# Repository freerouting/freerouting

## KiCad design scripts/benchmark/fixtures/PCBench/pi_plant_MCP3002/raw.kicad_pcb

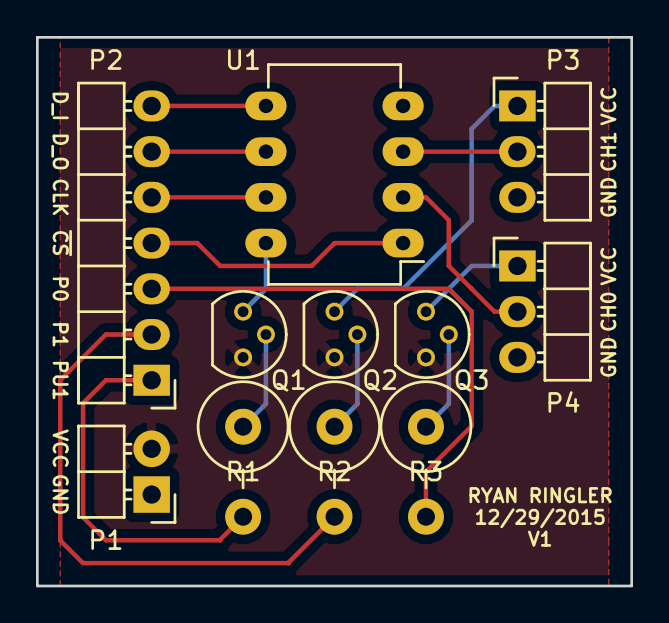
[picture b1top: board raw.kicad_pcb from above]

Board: 2 copper layers, 33.0 x 30.5 mm, 11 parts (0 on the bottom side), 17 nets.

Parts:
P1: CONN_01X02; Pin_Header_Angled_1x02_No_Pins
P2: CONN_01X07; Pin_Header_Angled_1x07_No_Pins
P3, P4: CONN_01X03; Pin_Header_Angled_1x03_No_Pins
Q1, Q2, Q3: 2N3904; TO-92_Molded_Narrow
R1, R2, R3: 1K; Resistor_Vertical_RM5mm
U1: MCP3002; DIP-8_W7.62mm_LongPads

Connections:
GND: P1.1, P3.3, P4.3, U1.4
unnamed: P2.1, R1.2
unnamed: P2.2, R2.2
unnamed: P2.3, R3.2
unnamed: P2.4, U1.1
unnamed: P2.5, U1.7
unnamed: P2.6, U1.6
unnamed: P2.7, U1.5
unnamed: P3.1, Q2.1
unnamed: P3.2, U1.3
unnamed: P4.1, Q3.1
unnamed: P4.2, U1.2
unnamed: Q1.1, U1.8
unnamed: Q1.2, R1.1
unnamed: Q2.2, R2.1
unnamed: Q3.2, R3.1
VCC: P1.2, Q1.3, Q2.3, Q3.3

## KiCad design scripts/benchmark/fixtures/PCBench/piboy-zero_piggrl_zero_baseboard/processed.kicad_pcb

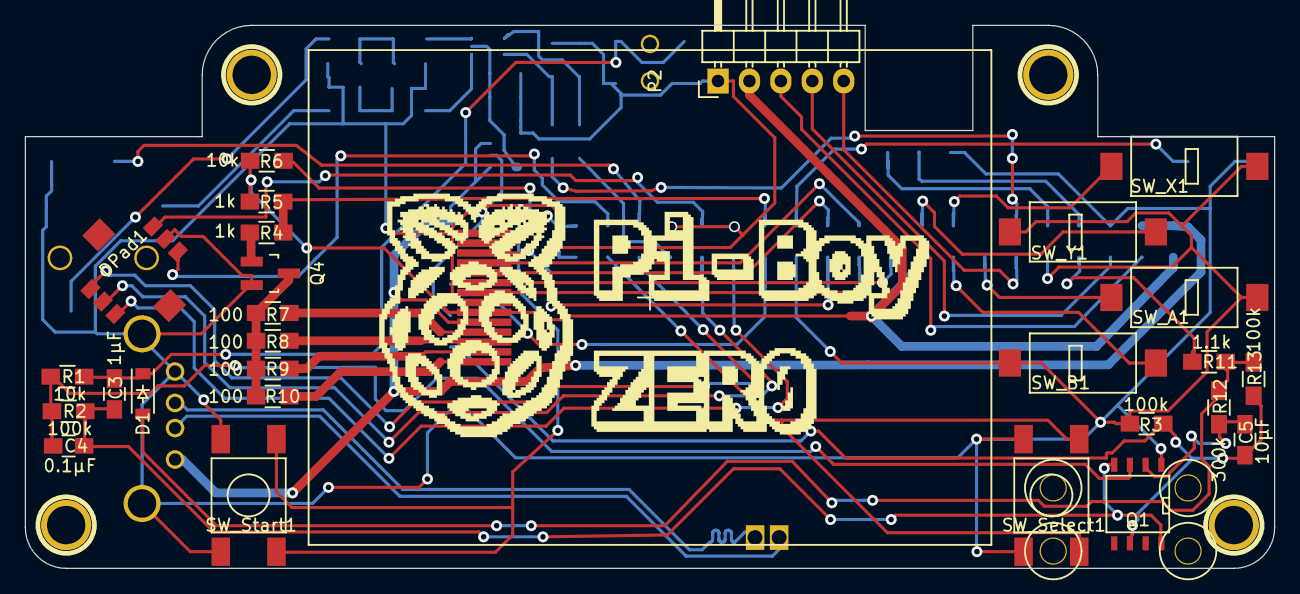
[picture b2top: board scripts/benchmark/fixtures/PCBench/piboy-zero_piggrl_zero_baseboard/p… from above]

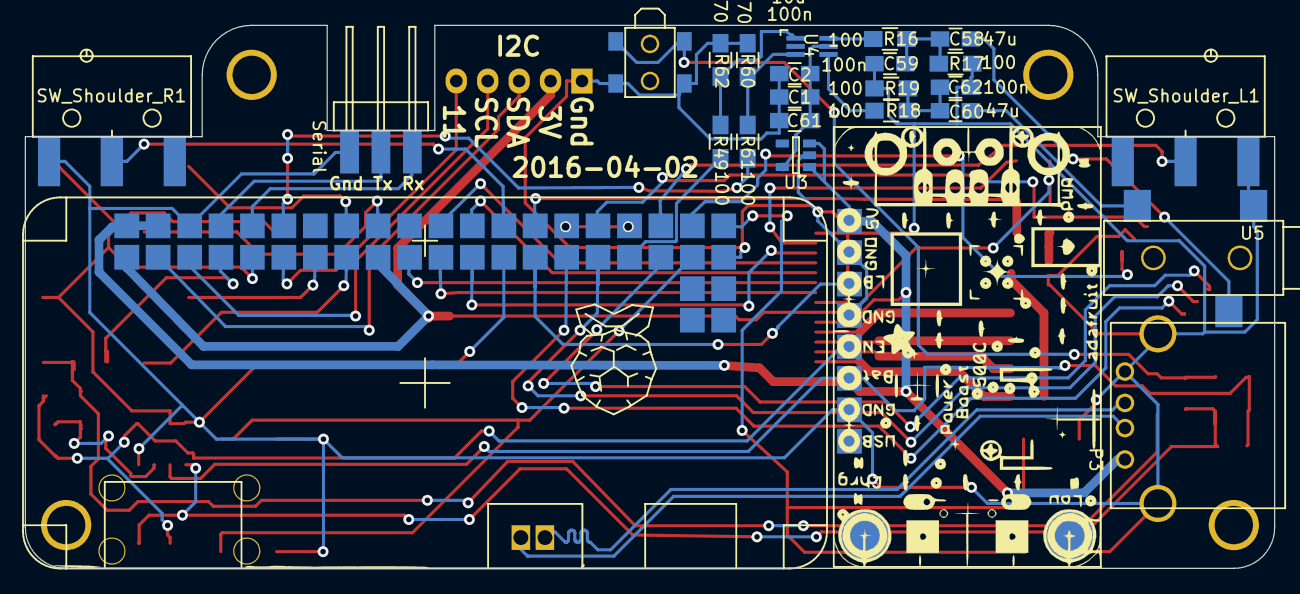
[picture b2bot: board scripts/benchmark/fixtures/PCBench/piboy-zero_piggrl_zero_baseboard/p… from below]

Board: 2 copper layers, 101.0 x 43.9 mm, 57 parts (25 on the bottom side), 55 nets.

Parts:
1PIN, 1PIN_2, 1PIN_3, 1PIN_4: P***; 1pin
C1: 10u; C_0805_HandSoldering
C2: 10n; C_0805_HandSoldering
C3: 1µF; C_0805_HandSoldering
C4: 0.1µF; C_0805_HandSoldering
C5: 10µF; C_0805_HandSoldering
C58, C60: 47u; C_0805_HandSoldering
C59, C61, C62: 100n; C_0805_HandSoldering
D1: D; SOD-123
DPad1: SKRHAAE010
P1: PowerBoost 500c; Powerboost500c
P2: I2C; Pin_Header_Angled_1x05
P3: USB_A
P4: Serial; 1x3_smd_pinheader
Q1: IRF7309IPBF; SOIC-8-N
Q4: MMBT2222; SOT-23_Handsoldering
R1, R6: 10k; R_0805_HandSoldering
R2, R3, R13: 100k; R_0805_HandSoldering
R4, R5: 1k; R_0805_HandSoldering
R7, R8, R9, R10, R16, R17, R18, R19, R49, R61: 100; R_0805_HandSoldering
R11: 1.1k; R_0805_HandSoldering
R12: 300k; R_0805_HandSoldering
R60, R62: 470; R_0805_HandSoldering
SW1: SW_PUSH; btn_1571262-1
SW_A1: SW_PUSH; Omron_D2LS_21_woKeyHoles
SW_B1: SW_PUSH; Omron_D2LS_21_woKeyHoles
SW_Select1: SW_PUSH; smd_push_button
SW_Shoulder_L1: SW_PUSH; Omron_D2FS_FTN_mirror
SW_Shoulder_R1: SW_PUSH; Omron_D2FS_FTN
SW_Start1: SW_PUSH; smd_push_button
SW_X1: SW_PUSH; Omron_D2LS_21_woKeyHoles
SW_Y1: SW_PUSH; Omron_D2LS_21_woKeyHoles
U1: gpio-header_zero; raspberry-zero
U2: 2.2_tft_ili9340; TM022HDH26
U3: Regulator_LP2980; SOT-23-5
U4: NC7WZ16_Dual_Buffer; SC-70-6_Handsoldering
U5: audio_jack; audio_smd_SJ-3523-SMT-TR

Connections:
+2V5: C1.1, C2.1, C61.2, U3.5, U4.5
+3V3: P2.2, R4.2, R6.2, U1.1, U1.17, U2.9
+5V: P1.8, P3.1, U1.2, U1.4, U2.10, U3.1, U3.3
+BATT: C4.2, P1.3, Q1.3, R1.2, R2.2
/LowBatOut: P1.6, U1.27
/PWM_backlight: R4.1, R5.2, U1.28
/Rasberppy B+ audio/Aud_PWM0: R61.2, U1.12
/Rasberppy B+ audio/Aud_PWM1: R49.2, U1.33
/USB_D+: P3.3, U1.46
/USB_D-: P3.2, U1.45
/btn_1: SW_A1.2, U1.13
/btn_2: SW_B1.2, U1.15
/btn_3: SW_X1.2, U1.16
/btn_4: SW_Y1.2, U1.18
/btn_5: SW_Shoulder_L1.2, U1.36
/btn_6: SW_Shoulder_R1.2, U1.26
/btn_7: SW_Start1.2, U1.40
/btn_8: SW_Select1.2, U1.37
/dpad_1: DPad1.2, U1.31
/dpad_2: DPad1.4, U1.32
/dpad_3: DPad1.3, U1.29
/dpad_4: DPad1.6, U1.38
/dpad_5: DPad1.1, U1.35
/soft_power_button/Pwr-On: R11.1, U1.7
/spi_1: U1.23, U2.3
/spi_2: U1.19, U2.6
/spi_3: U1.21, U2.7
Enable: C5.2, P1.4, Q1.6, R3.1, R13.2
GND: C1.2, C2.2, C59.1, C61.1, C62.1, DPad1.5, P1.2, P1.5, P1.7, P2.1, P3.4, P3.5, P4.1, Q1.1, Q4.2, R3.2, R17.2, R19.2, R60.2, R62.2, SW1.1, SW_A1.1, SW_B1.1, SW_Select1.1, SW_Shoulder_L1.1, SW_Shoulder_R1.1, SW_Start1.1, SW_X1.1, SW_Y1.1, U1.6, U1.9, U1.25, U1.30, U1.34, U1.39, U2.1, U2.8, U3.2, U5.1
unnamed: C3.1, C4.1, Q1.4, Q1.8, R2.1
unnamed: C3.2, D1.1, R1.1, SW1.2
unnamed: C5.1, Q1.2, R12.2
unnamed: C58.1, U5.3
unnamed: C58.2, C59.2, R16.1, R17.1
unnamed: C60.1, U5.2
unnamed: C60.2, C62.2, R18.1, R19.1
unnamed: D1.2, R11.2, R12.1, R13.1
unnamed: P2.3, U1.3
unnamed: P2.4, U1.5
unnamed: P2.5, U1.11
unnamed: P4.2, U1.8
unnamed: P4.3, U1.10
unnamed: Q4.1, R5.1
unnamed: Q4.3, R7.2, R8.2, R9.2, R10.2
unnamed: R6.1, U2.2
unnamed: R7.1, U2.11
unnamed: R8.1, U2.12
unnamed: R9.1, U2.13
unnamed: R10.1, U2.14
unnamed: R16.2, U4.6
unnamed: R18.2, U4.4
unnamed: R49.1, R62.1, U4.1
unnamed: R60.1, R61.1, U4.3
unnamed: U1.22, U2.4
unnamed: U1.24, U2.5

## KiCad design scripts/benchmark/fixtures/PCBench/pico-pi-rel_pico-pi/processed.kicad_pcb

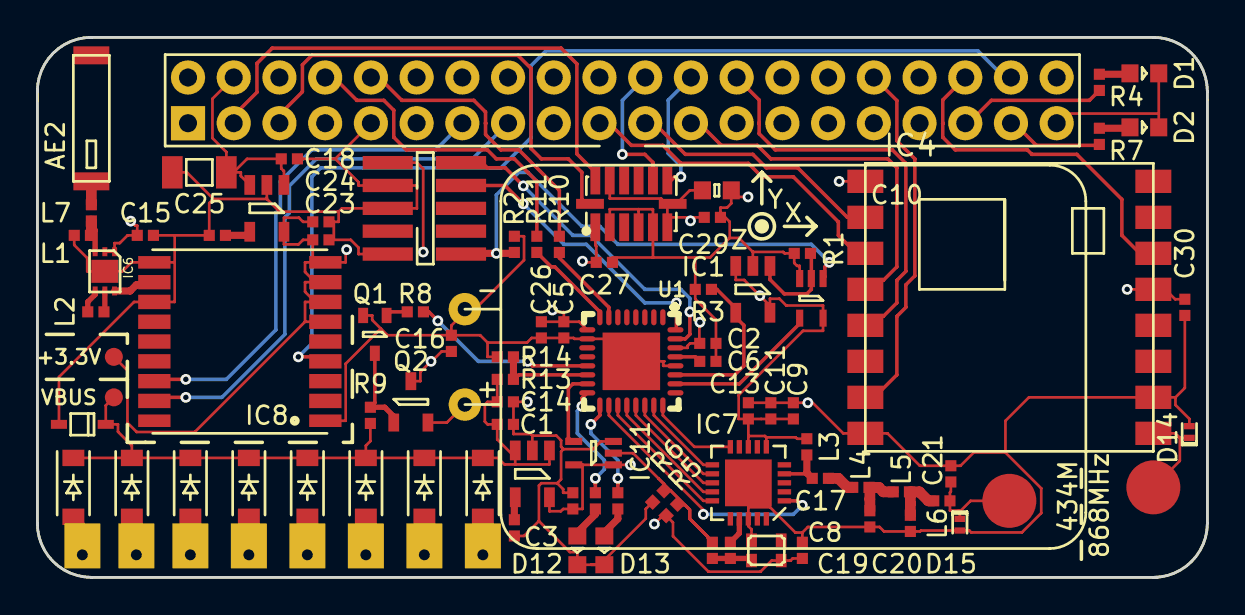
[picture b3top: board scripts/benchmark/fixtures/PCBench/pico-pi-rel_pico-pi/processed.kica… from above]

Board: 4 copper layers, 65.0 x 30.0 mm, 96 parts (0 on the bottom side), 73 nets.

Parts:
AE1, AE3: ANT; WIREPAD
AE2: ANT; 1575AT43A0040
C1, C4, C8, C15, C18, C24: 1µF; 0402
C2, C3, C6, C7, C11, C12, C14, C22, C26, C27, C29, C30: 100nF; 0402
C5, C13, C16: 100pF; 0402
C9: 2.2µF; 0402
C10: 5F,5.4V; PHV-5R4H505-R
C17, C20: 15pF; 0402
C19, C21: 8.2pF; 0402
C23: 10nF; 0402
C25: 100µF; 1206
C28: 10µF; 0603
D1: LED-WARN; 0603-LED
D2: LED-OK; 0603-LED
D3, D4, D5, D6, D7, D8, D9, D10: RB161M; SOD-123
D11: 5.1V; SOD-323
D12: LED-1; 0603-LED
D13: LED-2; 0603-LED
D14, D15: TVS_DIODE; TSLP-2-17
IC1: ADM6823T; SOT-23-5
IC2, IC9: TPS73633; SOT-23-5
IC3: 74LVC1G32; SC-70-5
IC4: RFM95_96_97_98W
IC5: TG-5006CJ
IC6: BGM1034N7; TSNP-7-10
IC7: Si4460; QFN-20-EP-SI
IC8: MAX-7Q
IC10: ADXL345; ADXL3x5
IC11: 74LVC1G126; SC-70-5
L1, L2: 8.2nH; 0402
L3: 470nH; 0402
L4: 56nH; 0402
L5, L6: 18nH; 0402
L7: NOSTUFF; 0402
P1: SWD; FTSH-105-01-L-DV-K
P2: Raspberry_Pi_+_Conn; Rasberry_Pi_Zero
P3, P4, P5, P6, P7, P8, P9, P10: PAD; 2mm_solder_pad
Q1: BC847CW; SOT-323
Q2: NX2301P; SOT-23
R1, R3: 1MΩ; 0402
R2, R8, R14: 10kΩ; 0402
R4, R7, R10, R11, R12, R15: 330Ω; 0402
R5, R6, R9: 100kΩ; 0402
R13: 33kΩ; 0402
TP1, TP2: TESTPAD
U1: ATSAMD20E17A-MU; QFN50P500X500X80-33

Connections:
16_TCXO: C7.2, C12.1, IC5.3
+3V3: C15.1, C23.1, C24.1, C27.1, C28.1, C29.1, C30.1, IC4.13, IC6.1, IC6.2, IC8.6, IC8.7, IC8.8, IC8.9, IC9.5, IC10.1, IC10.6, IC10.7, IC10.12, TP2.1
+5VP: C16.1, C18.1, C25.1, IC9.1, IC9.3, P2.2, P2.4, Q2.3
/868_ANT: AE1.1, D14.1, IC4.9
/A_RX: R11.1, U1.8
/A_TX: R10.1, U1.7
/EXT~RESET: IC3.1, P1.10, R2.1
/MAX_RF_IN: IC6.6, IC8.11
/SAM_TCXO: IC11.4, U1.15
/SI_ANT: AE3.1, C21.1, D15.1, L6.2
/SI_TCXO: C12.2, IC7.17
/SI_TX: C17.1, IC7.4, L3.2
/SWCLK: P1.4, U1.32
/SWDIO: P1.2, U1.31
/TCXO_BUF_IN: C7.1, IC11.2, R5.2, R6.1
/VBUS_SENSE: R13.2, R14.1, U1.14
/VP_CTRL: Q1.3, Q2.1, R9.2
/V_CORE: C6.1, U1.29
/WDI~RESET: IC1.1, IC3.2, R1.1
/~RST: IC3.4, U1.26
ADXL_INT1: IC10.8, P2.24
ADXL_INT2: IC10.9, P2.22
CE1/DIO0: IC4.14, P2.36
CE1/DIO5: IC4.7, P2.32
CE1/NSS: IC4.5, P2.26
GND: C1.2, C2.2, C3.2, C4.2, C5.2, C6.2, C8.2, C9.2, C10.2, C11.2, C13.2, C14.2, C15.2, C16.2, C18.2, C19.2, C20.2, C21.2, C22.2, C23.2, C24.2, C25.2, C26.2, C27.2, C28.2, C29.2, C30.2, D1.1, D2.1, D11.2, D12.1, D13.1, D14.2, D15.2, IC1.2, IC2.2, IC3.3, IC4.1, IC4.8, IC4.10, IC5.2, IC6.PAD, IC7.18, IC7.EP, IC8.1, IC8.10, IC8.12, IC9.2, IC10.2, IC10.4, IC10.5, IC11.3, L1.2, P1.3, P1.5, P1.9, P2.6, P2.9, P2.14, P2.20, P2.25, P2.30, P2.34, P2.39, Q1.2, R1.2, R2.2, R3.2, R6.2, R14.2, U1.10, U1.28, U1.33
LED_1: R12.1, U1.16
LED_2: R15.1, U1.17
LED_OK: P2.37, R7.1
LED_WARN: P2.35, R4.1
MISO: IC4.2, P2.21
MOSI: IC4.3, P2.19
unnamed: AE2.1, L7.1
unnamed: C3.1, IC2.4
unnamed: C17.2, L4.1
unnamed: C19.1, L4.2, L5.1
unnamed: C20.1, L5.2, L6.1
unnamed: C22.1, IC9.4
unnamed: D1.2, R4.2
unnamed: D2.2, R7.2
unnamed: D3.2, P3.1
unnamed: D4.2, P4.1
unnamed: D5.2, P5.1
unnamed: D6.2, P6.1
unnamed: D7.2, P7.1
unnamed: D8.2, P8.1
unnamed: D9.2, P9.1
unnamed: D10.2, P10.1
unnamed: D12.2, R12.2
unnamed: D13.2, R15.2
unnamed: IC6.3, L1.1, L7.2
unnamed: IC6.4, L2.1
unnamed: IC6.5, L2.2
unnamed: Q1.1, R8.2
PI_SCL: IC10.14, P2.5
PI_SDA: IC10.13, P2.3
SCK: IC4.4, P2.23
SI_GPIO1: IC7.10, U1.24
SI_MISO: IC7.13, U1.21
SI_MOSI: IC7.14, U1.20
SI_SCLK: IC7.12, U1.22
SI_SDN: IC7.1, U1.18
SI_~IRQ: IC7.11, U1.23
SI_~SEL: IC7.15, U1.19
UART_PIAO: P2.10, R10.2
UART_POAI: P2.8, R11.2
UBX_SCL: IC8.17, P2.15
UBX_SDA: IC8.16, P2.13
UBX_TIMEPULSE: IC8.4, P2.38
VBUS: C1.1, C10.1, C14.1, D3.1, D4.1, D5.1, D6.1, D7.1, D8.1, D9.1, D10.1, D11.1, IC2.1, IC2.3, Q2.2, R9.1, R13.1, TP1.1
VDD: C2.1, C4.1, C5.1, C8.1, C9.1, C11.1, C13.1, C26.1, IC1.3, IC1.5, IC2.5, IC3.5, IC5.4, IC7.6, IC7.8, IC11.1, IC11.5, L3.1, P1.1, R5.1, U1.9, U1.30
VP_EN: R8.1, U1.13
WDI: IC1.4, R3.1, U1.27
